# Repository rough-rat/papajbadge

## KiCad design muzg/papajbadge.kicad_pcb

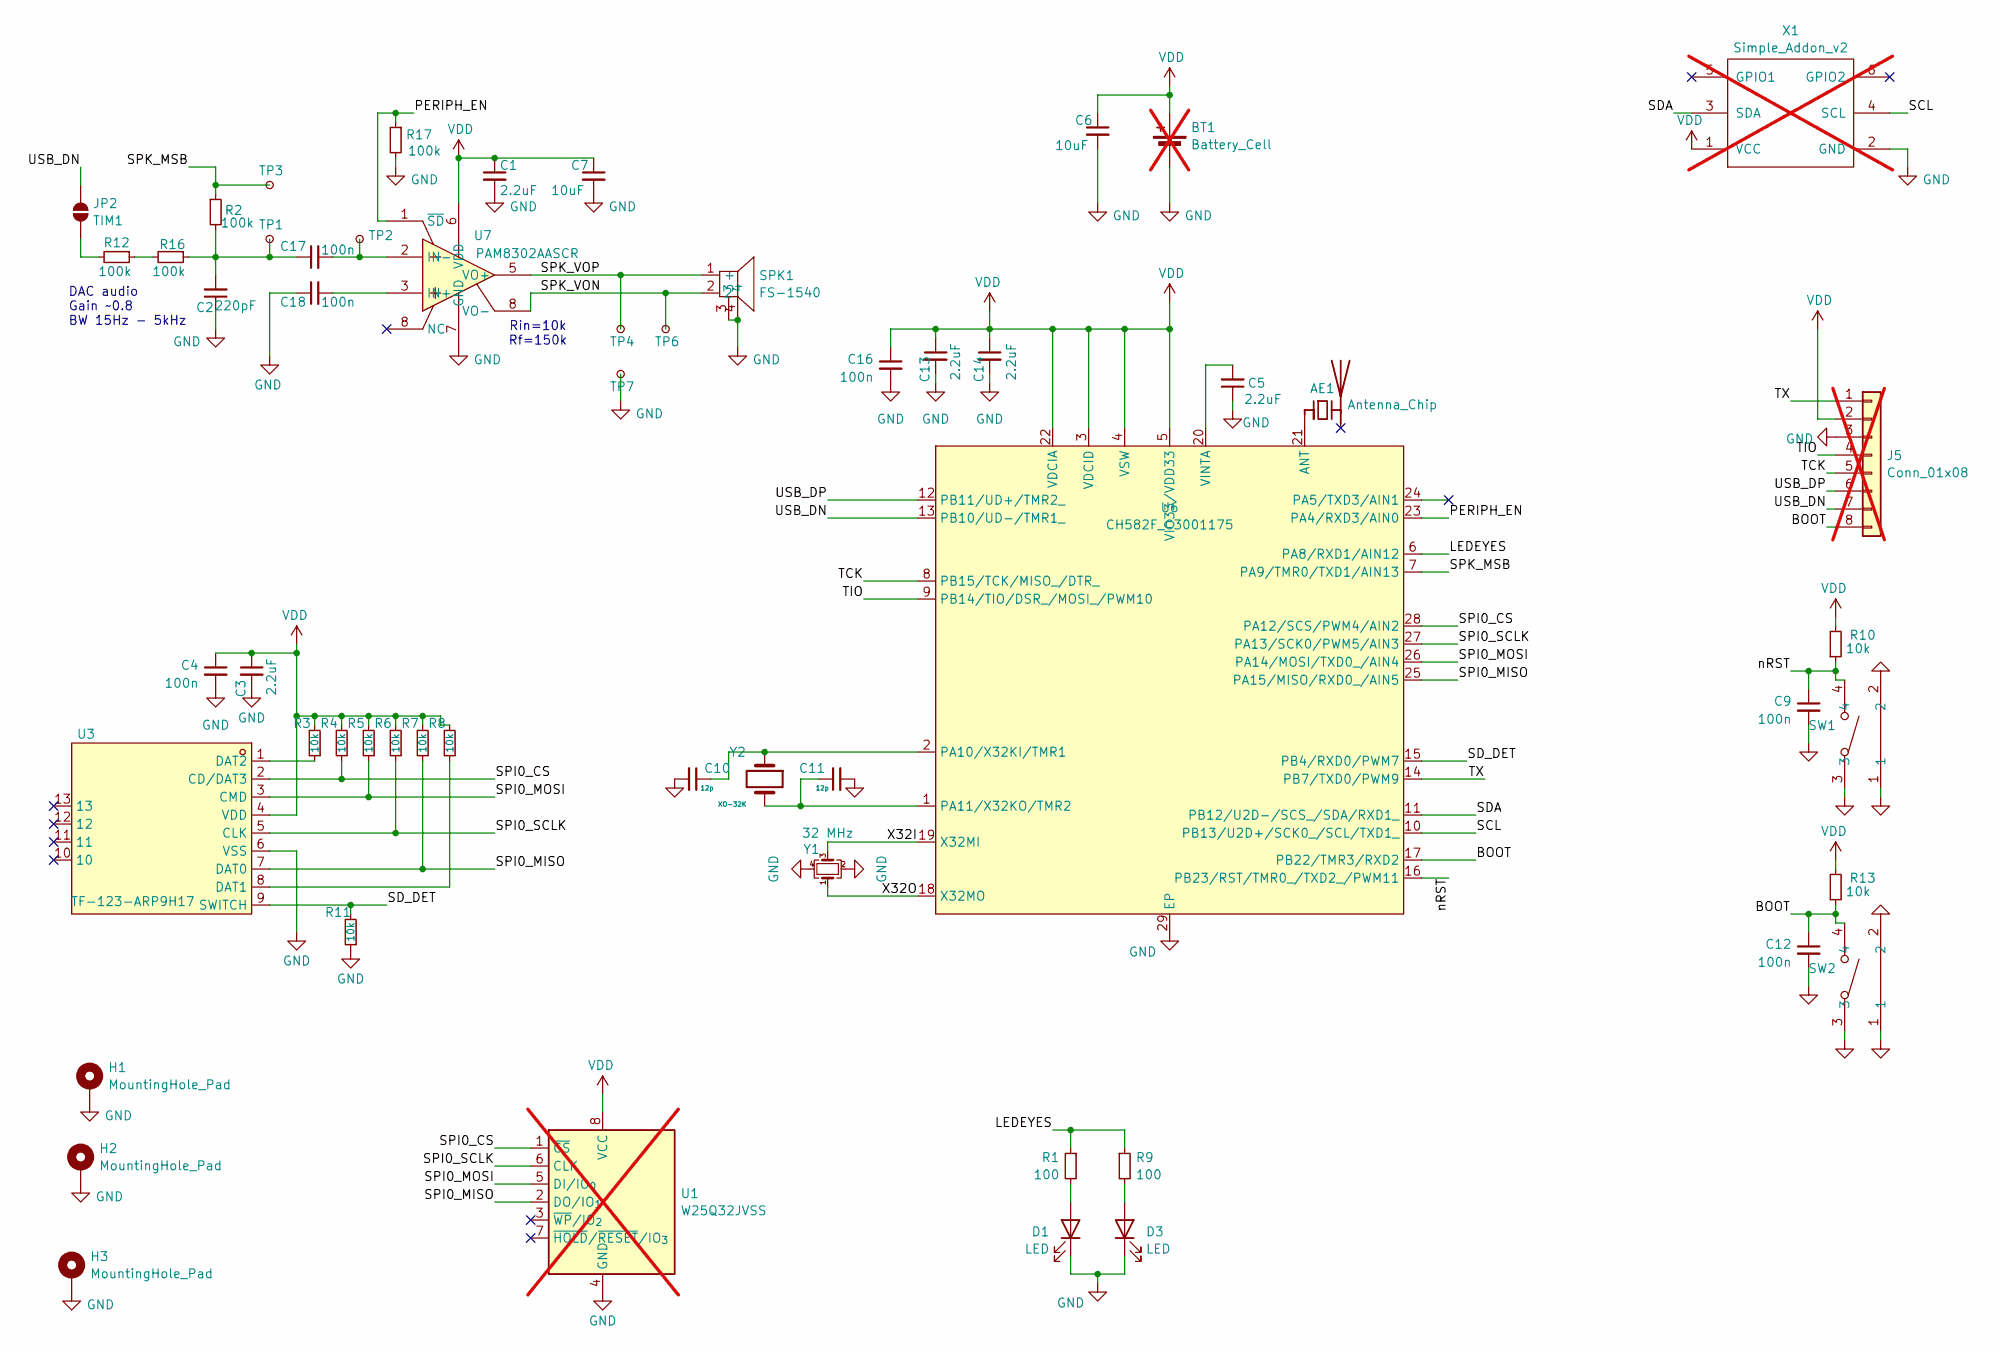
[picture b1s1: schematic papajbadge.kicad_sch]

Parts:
AE1: Antenna_Chip; Johanson_2450AT18x100; LCSC C127629
BT1: Battery_Cell; BatteryHolder_Multicomp_BC-2001_1x2032; not fitted
C1, C3, C5, C13, C14: 2.2uF; C_0402_1005Metric
C2: 220pF; C_0402_1005Metric
C4, C9, C12, C16, C17, C18: 100n; C_0402_1005Metric
C6, C7: 10uF; C_0603_1608Metric
C10, C11: 12p; C_0402_1005Metric
D1, D3: LED; LED_0603_1608Metric
H1, H2, H3: MountingHole_Pad; MountingHole_2.7mm_M2.5_DIN965_Pad
J5: Conn_01x08; PinSocket_1x08_P2.54mm_Vertical; not fitted
JP2: TIM1; SolderJumper-2_P1.3mm_Open_RoundedPad1.0x1.5mm
R1, R9: 100; R_0402_1005Metric
R2, R12, R16, R17: 100k; R_0402_1005Metric
R3, R4, R5, R6, R7, R8, R10, R11, R13: 10k; R_0402_1005Metric
SPK1: FS-1540; BUZ-SMD_5P-L15.0-W15.0-P13.7-BL; LCSC C482341
SW1, SW2: TS24CA; SW-SMD_TS24CA; LCSC C393942
TP1, TP2, TP3: RX; TestPoint_Pad_D0.6mm
TP4, TP6, TP7: RX; TestPoint_Pad_D1.0mm
U1: W25Q32JVSS; SOIC-8_5.3x5.3mm_P1.27mm; not fitted
U3: TF-123-ARP9H17; TF-SMD_TF-123-ARP9H15; LCSC C2982548
U6: CH582F_C3001175; QFN-28_L4.0-W4.0-P0.40-BL-EP2.8; LCSC C3001175
U7: PAM8302AASCR; MSOP-8_L3.0-W3.0-P0.65-LS5.0-BL; LCSC C113367
X1: Simple_Addon_v2; PinHeader_2x03_P2.54mm_Vertical; not fitted
Y1: 32 MHz; Crystal_SMD_2016-4Pin_2.0x1.6mm; LCSC C2682773
Y2: XO-32K; Crystal_SMD_2012-2Pin_2.0x1.2mm; LCSC C7500573

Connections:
/BOOT: C12.1, J5.8, R13.1, SW2.4, U6.17 (PB22/TMR3/RXD2)
/LEDEYES: R1.1, R9.1, U6.6 (PA8/RXD1/AIN12)
/PERIPH_EN: R17.1, U6.23 (PA4/RXD3/AIN0), U7.1 (~SD)
/SCL: U6.10 (PB13/U2D+/SCK0_/SCL/TXD1_), X1.4 (SCL)
/SDA: U6.11 (PB12/U2D-/SCS_/SDA/RXD1_), X1.3 (SDA)
/SD_DET: R11.2, U3.9 (SWITCH), U6.15 (PB4/RXD0/PWM7)
/SPI0_CS: R4.1, U1.1 (~CS), U3.2 (CD/DAT3), U6.28 (PA12/SCS/PWM4/AIN2)
/SPI0_MISO: R7.1, U1.2 (DO/IO_{1}), U3.7 (DAT0), U6.25 (PA15/MISO/RXD0_/AIN5)
/SPI0_MOSI: R5.1, U1.5 (DI/IO_{0}), U3.3 (CMD), U6.26 (PA14/MOSI/TXD0_/AIN4)
/SPI0_SCLK: R6.1, U1.6 (CLK), U3.5 (CLK), U6.27 (PA13/SCK0/PWM5/AIN3)
/SPK_MSB: R2.1, TP3.1, U6.7 (PA9/TMR0/TXD1/AIN13)
/SPK_VON: SPK1.2, TP6.1, U7.8 (VO-)
/SPK_VOP: SPK1.1 (+), TP4.1, U7.5 (VO+)
/TCK: J5.5, U6.8 (PB15/TCK/MISO_/DTR_)
/TIO: J5.4, U6.9 (PB14/TIO/DSR_/MOSI_/PWM10)
/TX: J5.1, U6.14 (PB7/TXD0/PWM9)
/USB_DN: J5.7, JP2.2 (B), U6.13 (PB10/UD-/TMR1_)
/USB_DP: J5.6, U6.12 (PB11/UD+/TMR2_)
/X32I: U6.19 (X32MI), Y1.3
/X32O: U6.18 (X32MO), Y1.1
/nRST: C9.1, R10.1, SW1.4, U6.16 (PB23/RST/TMR0_/TXD2_/PWM11)
GND: BT1.2 (-), C1.2, C2.1, C3.2, C4.2, C5.1, C6.2, C7.2, C9.2, C10.2, C11.2, C12.2, C13.2, C14.2, C16.2, C18.1, D1.1 (K), D3.1 (K), H1.1, H2.1, H3.1, J5.3, R11.1, R17.2, SPK1.3, SPK1.4, SW1.1, SW1.2, SW1.3, SW2.1, SW2.2, SW2.3, TP7.1, U1.4 (GND), U3.6 (VSS), U6.29 (EP), U7.7 (GND), X1.2 (GND), Y1.2, Y1.4
unnamed: AE1.1 (FEED), U6.21 (ANT)
unnamed: C2.2, C17.1, R2.2, R16.1, TP1.1
unnamed: D1.2 (A), R1.2
unnamed: D3.2 (A), R9.2
unnamed: JP2.1 (A), R12.2
unnamed: R12.1, R16.2
unnamed: R8.1, U3.8 (DAT1)
unnamed: R3.1, U3.1 (DAT2)
unnamed: C10.1, U6.2 (PA10/X32KI/TMR1), Y2.1
unnamed: C11.1, U6.1 (PA11/X32KO/TMR2), Y2.2
unnamed: C5.2, U6.20 (VINTA)
unnamed: C18.2, U7.3 (IN+)
unnamed: C17.2, TP2.1, U7.2 (IN-)
VDD: BT1.1 (+), C1.1, C3.1, C4.1, C6.1, C7.1, C13.1, C14.1, C16.1, J5.2, R3.2, R4.2, R5.2, R6.2, R7.2, R8.2, R10.2, R13.2, U1.8 (VCC), U3.4 (VDD), U6.3 (VDCID), U6.4 (VSW), U6.5 (VIO33/VDD33), U6.22 (VDCIA), U7.6 (VDD), X1.1 (VCC)

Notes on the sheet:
Rin=10k Rf=150k
DAC audio Gain ~0.8 BW 15Hz - 5kHz

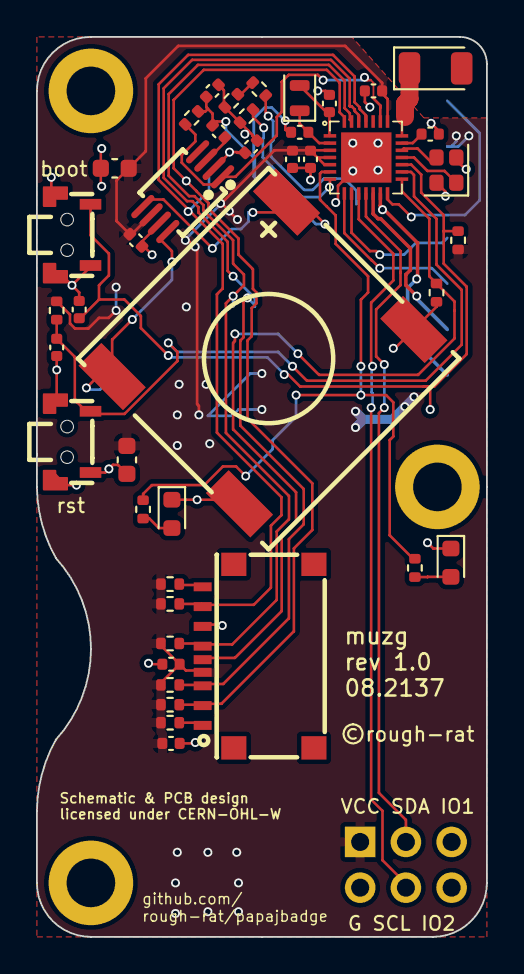
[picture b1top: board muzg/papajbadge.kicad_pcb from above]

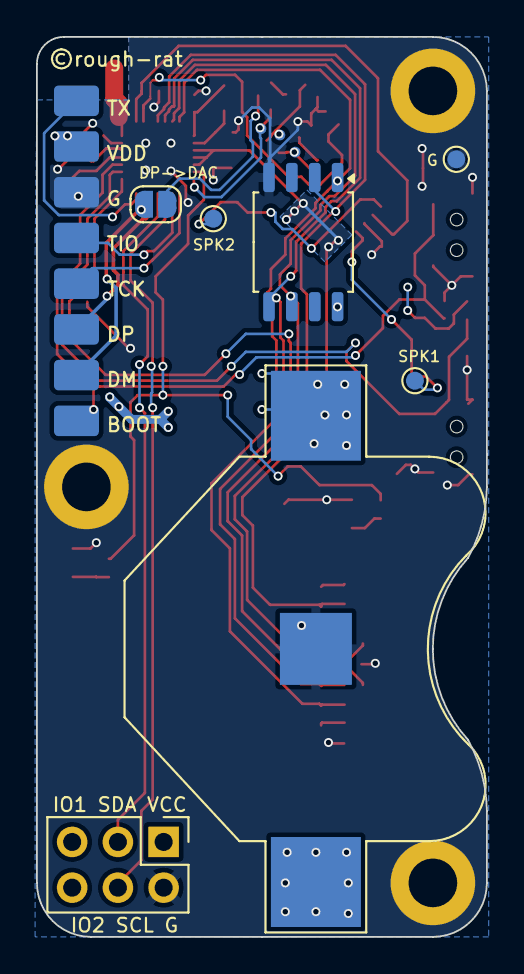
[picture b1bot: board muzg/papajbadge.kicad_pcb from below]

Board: 2 copper layers, 25.0 x 50.0 mm, 56 parts (12 on the bottom side), 36 nets.

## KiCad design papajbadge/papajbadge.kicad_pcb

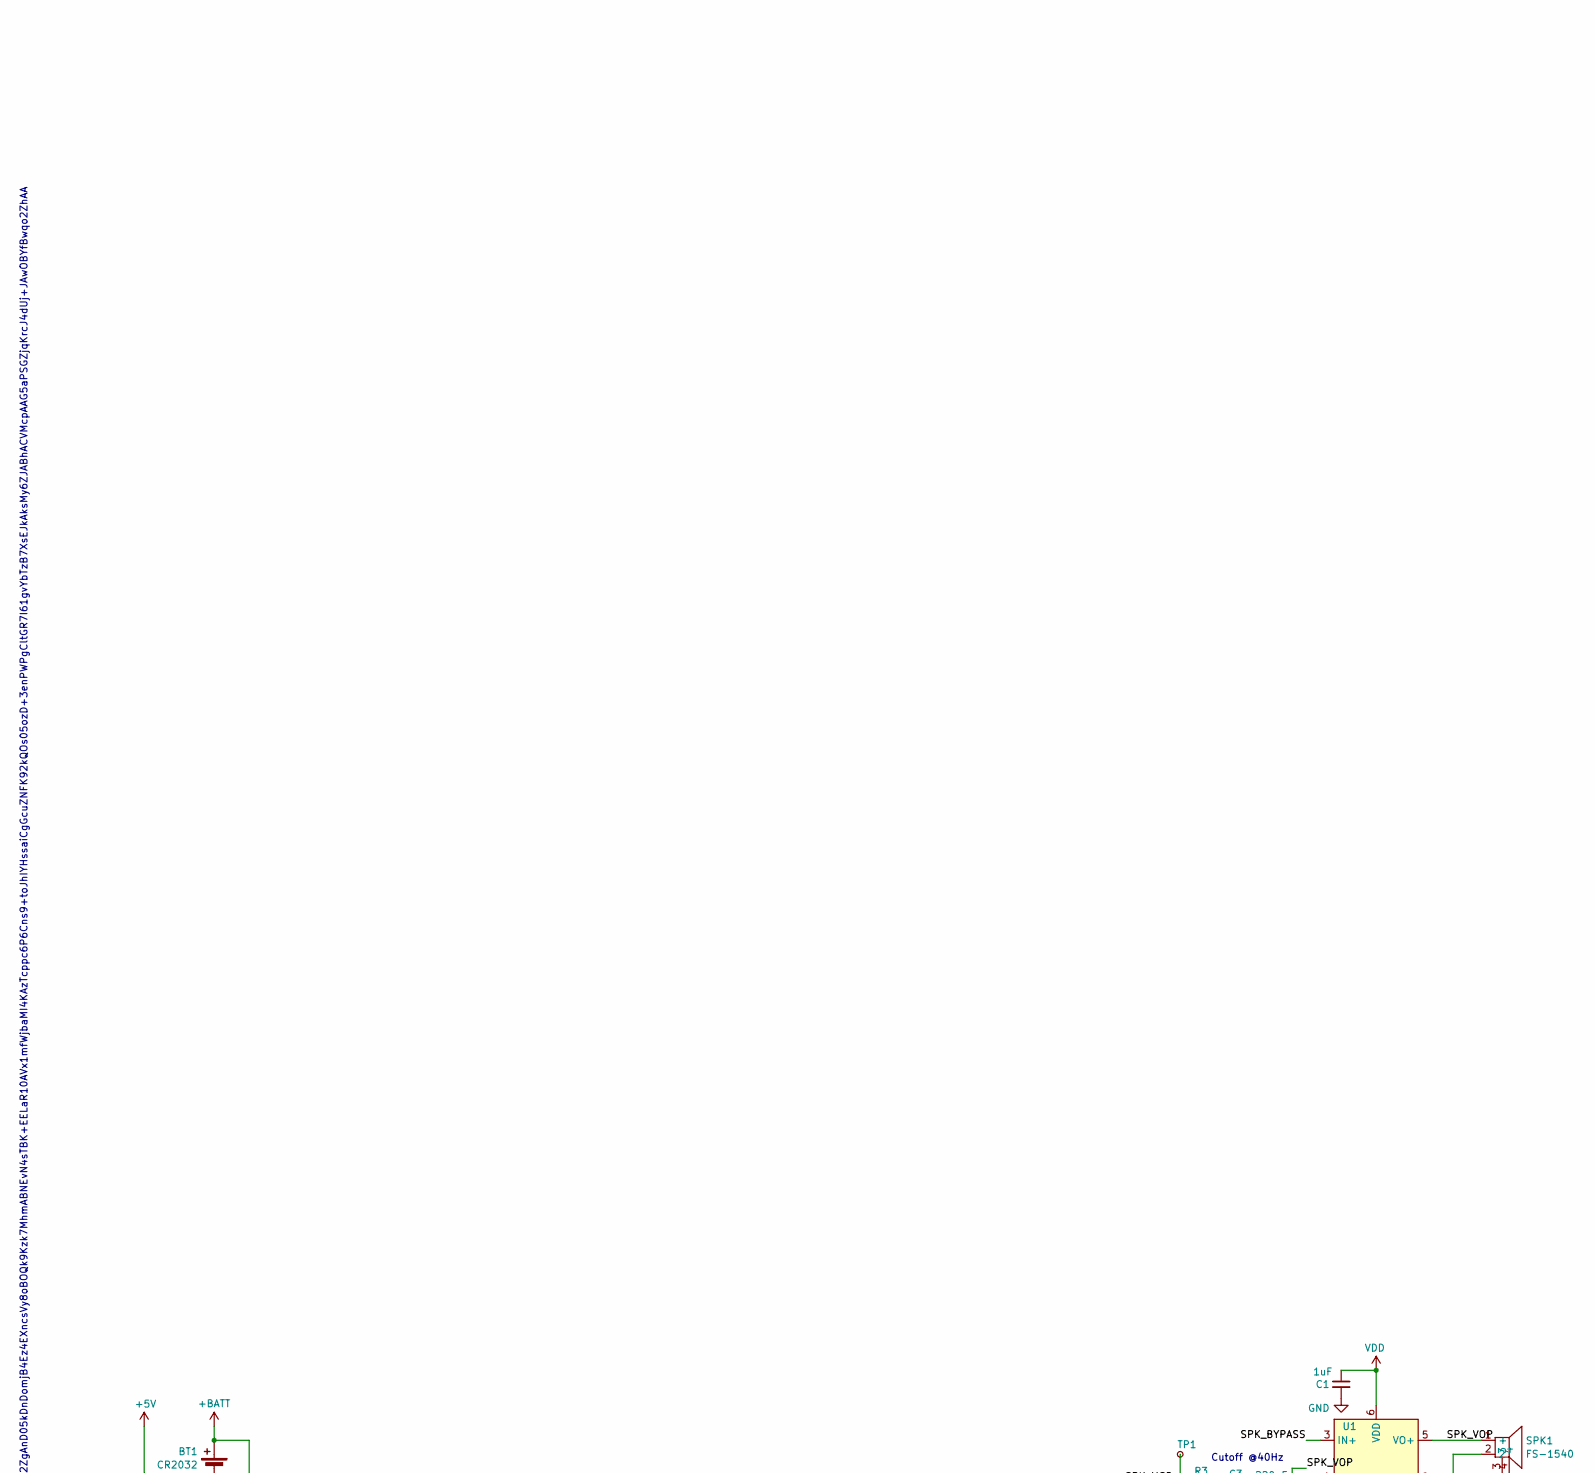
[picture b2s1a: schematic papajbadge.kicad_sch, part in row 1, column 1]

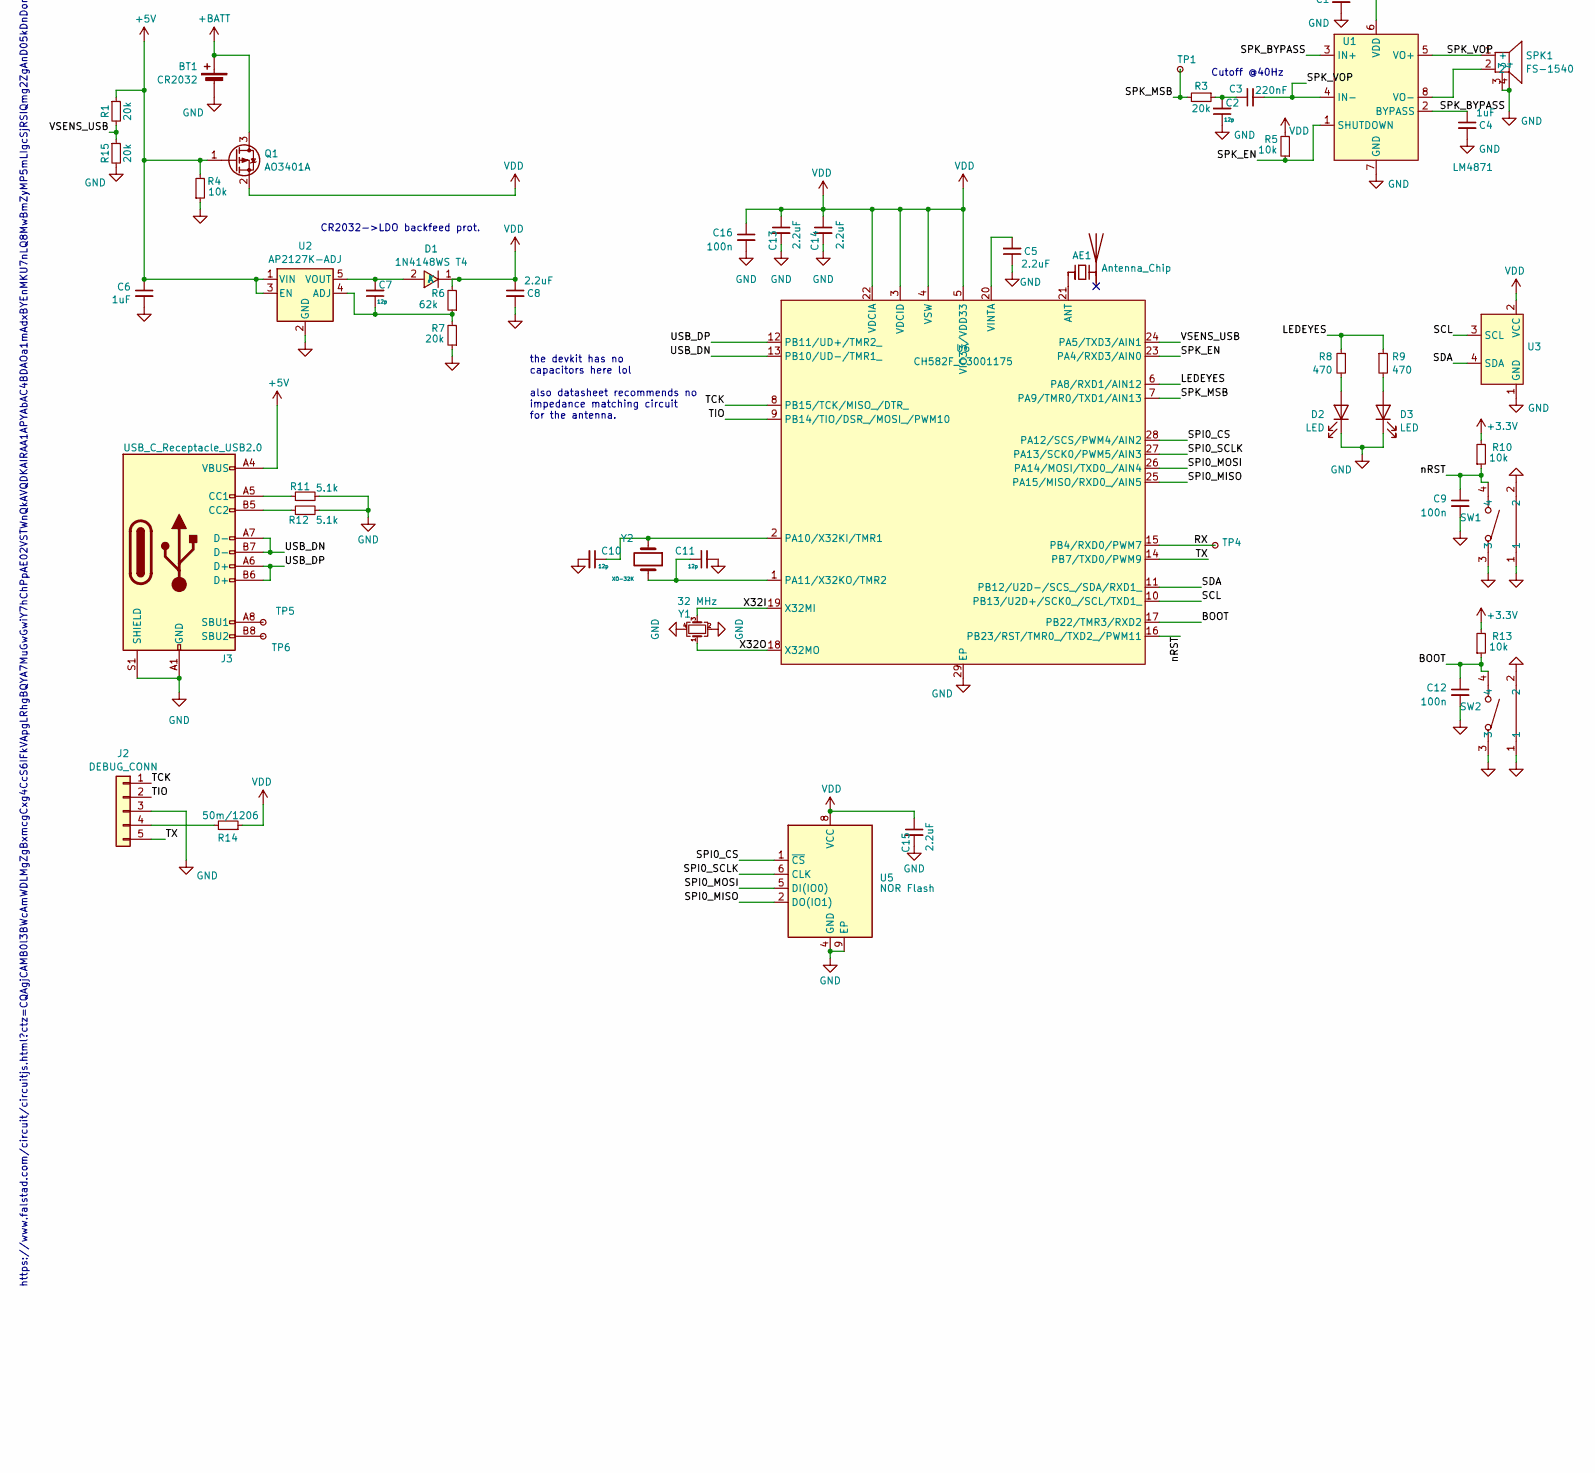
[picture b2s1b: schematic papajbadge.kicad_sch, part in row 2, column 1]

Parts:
AE1: Antenna_Chip; Johanson_2450AT18x100; LCSC C127629
BT1: CR2032; BatteryHolder_Multicomp_BC-2001_1x2032
C1, C4: 1uF; C_0402_1005Metric
C2, C7, C10, C11: 12p; C_0402_1005Metric; LCSC C1547
C3: 220nF; C_0402_1005Metric
C5, C8, C13, C14, C15: 2.2uF; C_0402_1005Metric
C6: 1uF; C_0402_1005Metric; LCSC C52923
C9, C12, C16: 100n; C_0402_1005Metric; LCSC C1525
D1: 1N4148WS T4; SOD-323_L1.8-W1.3-LS2.5-RD; LCSC Part C2128
D2, D3: LED; eyeled
J2: DEBUG_CONN; PinHeader_1x05_P2.54mm_Vertical
J3: USB_C_Receptacle_USB2.0; USB_C_Receptacle_HRO_TYPE-C-31-M-12; LCSC C165948
Q1: AO3401A; SOT-23
R1, R3, R7, R15: 20k; R_0402_1005Metric; LCSC C25741
R4, R5: 10k; R_0402_1005Metric; LCSC C25741
R6: 62k; R_0805_2012Metric; LCSC C17783
R8, R9: 470; LED_0805_2012Metric_Pad1.15x1.40mm_HandSolder
R10, R13: 10k; R_0402_1005Metric
R11, R12: 5.1k; R_0402_1005Metric
R14: 50m/1206; R_1206_3216Metric
SPK1: FS-1540; BUZ-SMD_5P-L15.0-W15.0-P13.7-BL; LCSC Part C482341
SW1, SW2: TS24CA; SW-SMD_TS24CA; LCSC C393942
TP1, TP4, TP5, TP6: RX; TestPoint_Pad_D0.6mm
U1: LM4871; SOIC-8_L4.9-W3.9-P1.27-LS6.0-BL; LCSC Part C7494970
U2: AP2127K-ADJ; SOT-23-5; LCSC C96343
U3: PinHeader_1x04_P2.54mm_Vertical
U5: NOR Flash; USON-8_2x3; LCSC C2843335
U6: CH582F_C3001175; QFN-28_L4.0-W4.0-P0.40-BL-EP2.8; LCSC Part C3001175
Y1: 32 MHz; Crystal_SMD_2016-4Pin_2.0x1.6mm
Y2: XO-32K; Crystal_SMD_2012-2Pin_2.0x1.2mm; LCSC C7500573

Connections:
+3.3V: R10.2, R13.2
+5V: C6.1, J3.A4 (VBUS), J3.A9 (VBUS), J3.B4 (VBUS), J3.B9 (VBUS), Q1.1 (G), R1.1, R4.2, U2.1 (VIN), U2.3 (EN)
+BATT: BT1.1 (+), Q1.3 (D)
/BOOT: C12.1, R13.1, SW2.4, U6.17 (PB22/TMR3/RXD2)
/LEDEYES: R8.1, R9.1, U6.6 (PA8/RXD1/AIN12)
/RX: TP4.1, U6.15 (PB4/RXD0/PWM7)
/SCL: U3.3 (SCL), U6.10 (PB13/U2D+/SCK0_/SCL/TXD1_)
/SDA: U3.4 (SDA), U6.11 (PB12/U2D-/SCS_/SDA/RXD1_)
/SPI0_CS: U5.1 (~CS), U6.28 (PA12/SCS/PWM4/AIN2)
/SPI0_MISO: U5.2 (DO(IO1)), U6.25 (PA15/MISO/RXD0_/AIN5)
/SPI0_MOSI: U5.5 (DI(IO0)), U6.26 (PA14/MOSI/TXD0_/AIN4)
/SPI0_SCLK: U5.6 (CLK), U6.27 (PA13/SCK0/PWM5/AIN3)
/SPK_BYPASS: C4.1, U1.2 (BYPASS), U1.3 (IN+)
/SPK_EN: R5.1, U1.1 (SHUTDOWN), U6.23 (PA4/RXD3/AIN0)
/SPK_MSB: R3.2, TP1.1, U6.7 (PA9/TMR0/TXD1/AIN13)
/SPK_VOP: C3.2, SPK1.1 (+), U1.4 (IN-), U1.5 (VO+)
/TCK: J2.1, U6.8 (PB15/TCK/MISO_/DTR_)
/TIO: J2.2, U6.9 (PB14/TIO/DSR_/MOSI_/PWM10)
/TX: J2.5, U6.14 (PB7/TXD0/PWM9)
/USB_DN: J3.A7 (D-), J3.B7 (D-), U6.13 (PB10/UD-/TMR1_)
/USB_DP: J3.A6 (D+), J3.B6 (D+), U6.12 (PB11/UD+/TMR2_)
/VSENS_USB: R1.2, R15.1, U6.24 (PA5/TXD3/AIN1)
/X32I: U6.19 (X32MI), Y1.3
/X32O: U6.18 (X32MO), Y1.1
/nRST: C9.1, R10.1, SW1.4, U6.16 (PB23/RST/TMR0_/TXD2_/PWM11)
GND: BT1.2 (-), C1.2, C2.1, C4.2, C5.1, C6.2, C8.2, C9.2, C10.2, C11.2, C12.2, C13.2, C14.2, C15.2, C16.2, D2.1 (K), D3.1 (K), J2.3, J3.A1 (GND), J3.A12 (GND), J3.B1 (GND), J3.B12 (GND), J3.S1 (SHIELD), R4.1, R7.1, R11.2, R12.2, R15.2, SPK1.3, SPK1.4, SW1.1, SW1.2, SW1.3, SW2.1, SW2.2, SW2.3, U1.7 (GND), U2.2 (GND), U3.1 (GND), U5.4 (GND), U5.9 (EP), U6.29 (EP), Y1.2, Y1.4
unnamed: AE1.1 (FEED), U6.21 (ANT)
unnamed: C2.2, C3.1, R3.1
unnamed: C7.2, D1.2 (A), U2.5 (VOUT)
unnamed: D2.2 (A), R8.2
unnamed: D3.2 (A), R9.2
unnamed: J2.4, R14.2
unnamed: J3.A5 (CC1), R11.1
unnamed: J3.B5 (CC2), R12.1
unnamed: J3.A8 (SBU1), TP5.1
unnamed: J3.B8 (SBU2), TP6.1
unnamed: SPK1.2, U1.8 (VO-)
unnamed: C7.1, R6.1, R7.2, U2.4 (ADJ)
unnamed: C10.1, U6.2 (PA10/X32KI/TMR1), Y2.1
unnamed: C11.1, U6.1 (PA11/X32KO/TMR2), Y2.2
unnamed: C5.2, U6.20 (VINTA)
VDD: C1.1, C8.1, C13.1, C14.1, C15.1, C16.1, D1.1 (K), Q1.2 (S), R5.2, R6.2, R14.1, U1.6 (VDD), U3.2 (VCC), U5.8 (VCC), U6.3 (VDCID), U6.4 (VSW), U6.5 (VIO33/VDD33), U6.22 (VDCIA)

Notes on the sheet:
CR2032->LDO backfeed prot.
Cutoff @40Hz
the devkit has no capacitors here lol also datasheet recommends no impedance matching circuit for the antenna.
https://www.falstad.com/circuit/circuitjs.html?ctz=CQAgjCAMB0l3BWcAmWDLMgZgBxmcgCxg4CcS6IFkVApgLRhgBQYA7MuGwGwiY7hChPpAE02VSTWnQkAVQDKAIRAA1APYAbAC4BDAOa1mAdxBYEnMKU7nLQ8MwBmZyMP5mLIgcSjRSIQmg2ZgAnD05kDnDomjB4Ez4EXncsVy8oBOQk9Kzk7MhmABNEvN4sTBK+EELaR10AVx1mfWjbaMI4KAzTcppc6P6Cns9+toJhIYHssaiCgGcuZN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

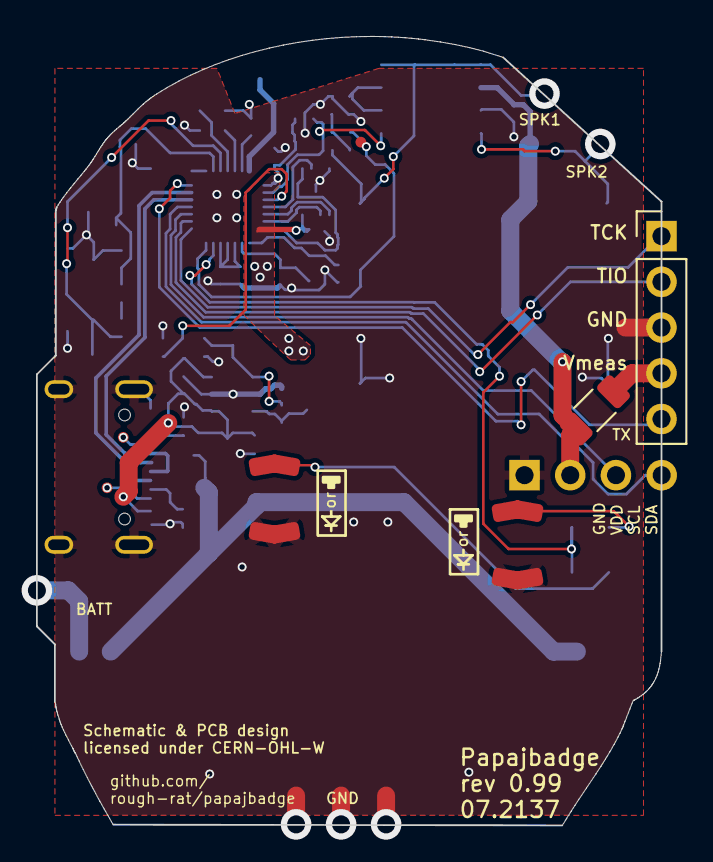
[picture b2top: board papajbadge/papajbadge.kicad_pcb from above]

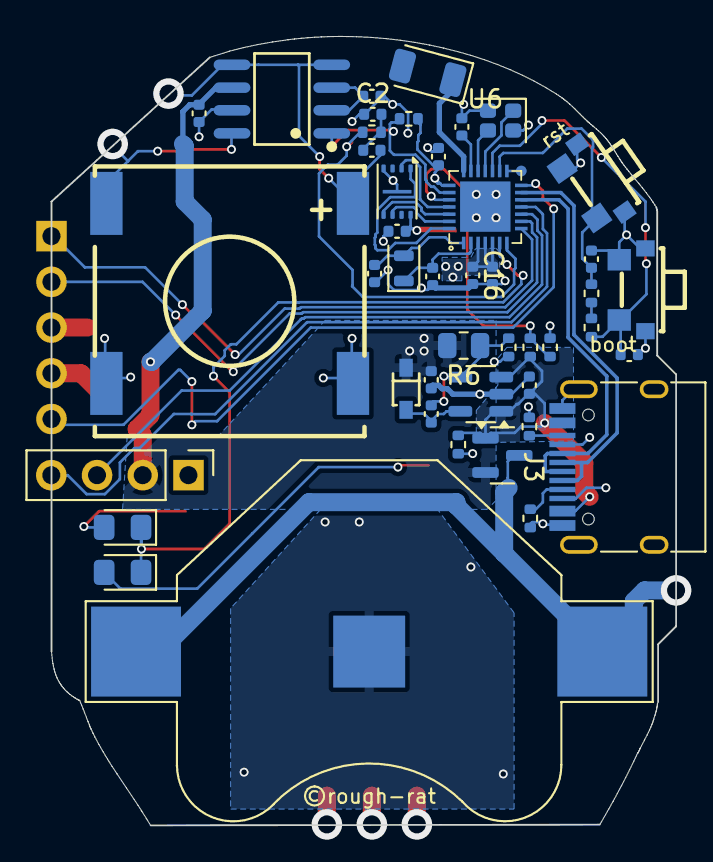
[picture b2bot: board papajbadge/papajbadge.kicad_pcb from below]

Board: 2 copper layers, 34.7 x 43.8 mm, 52 parts (45 on the bottom side), 42 nets.

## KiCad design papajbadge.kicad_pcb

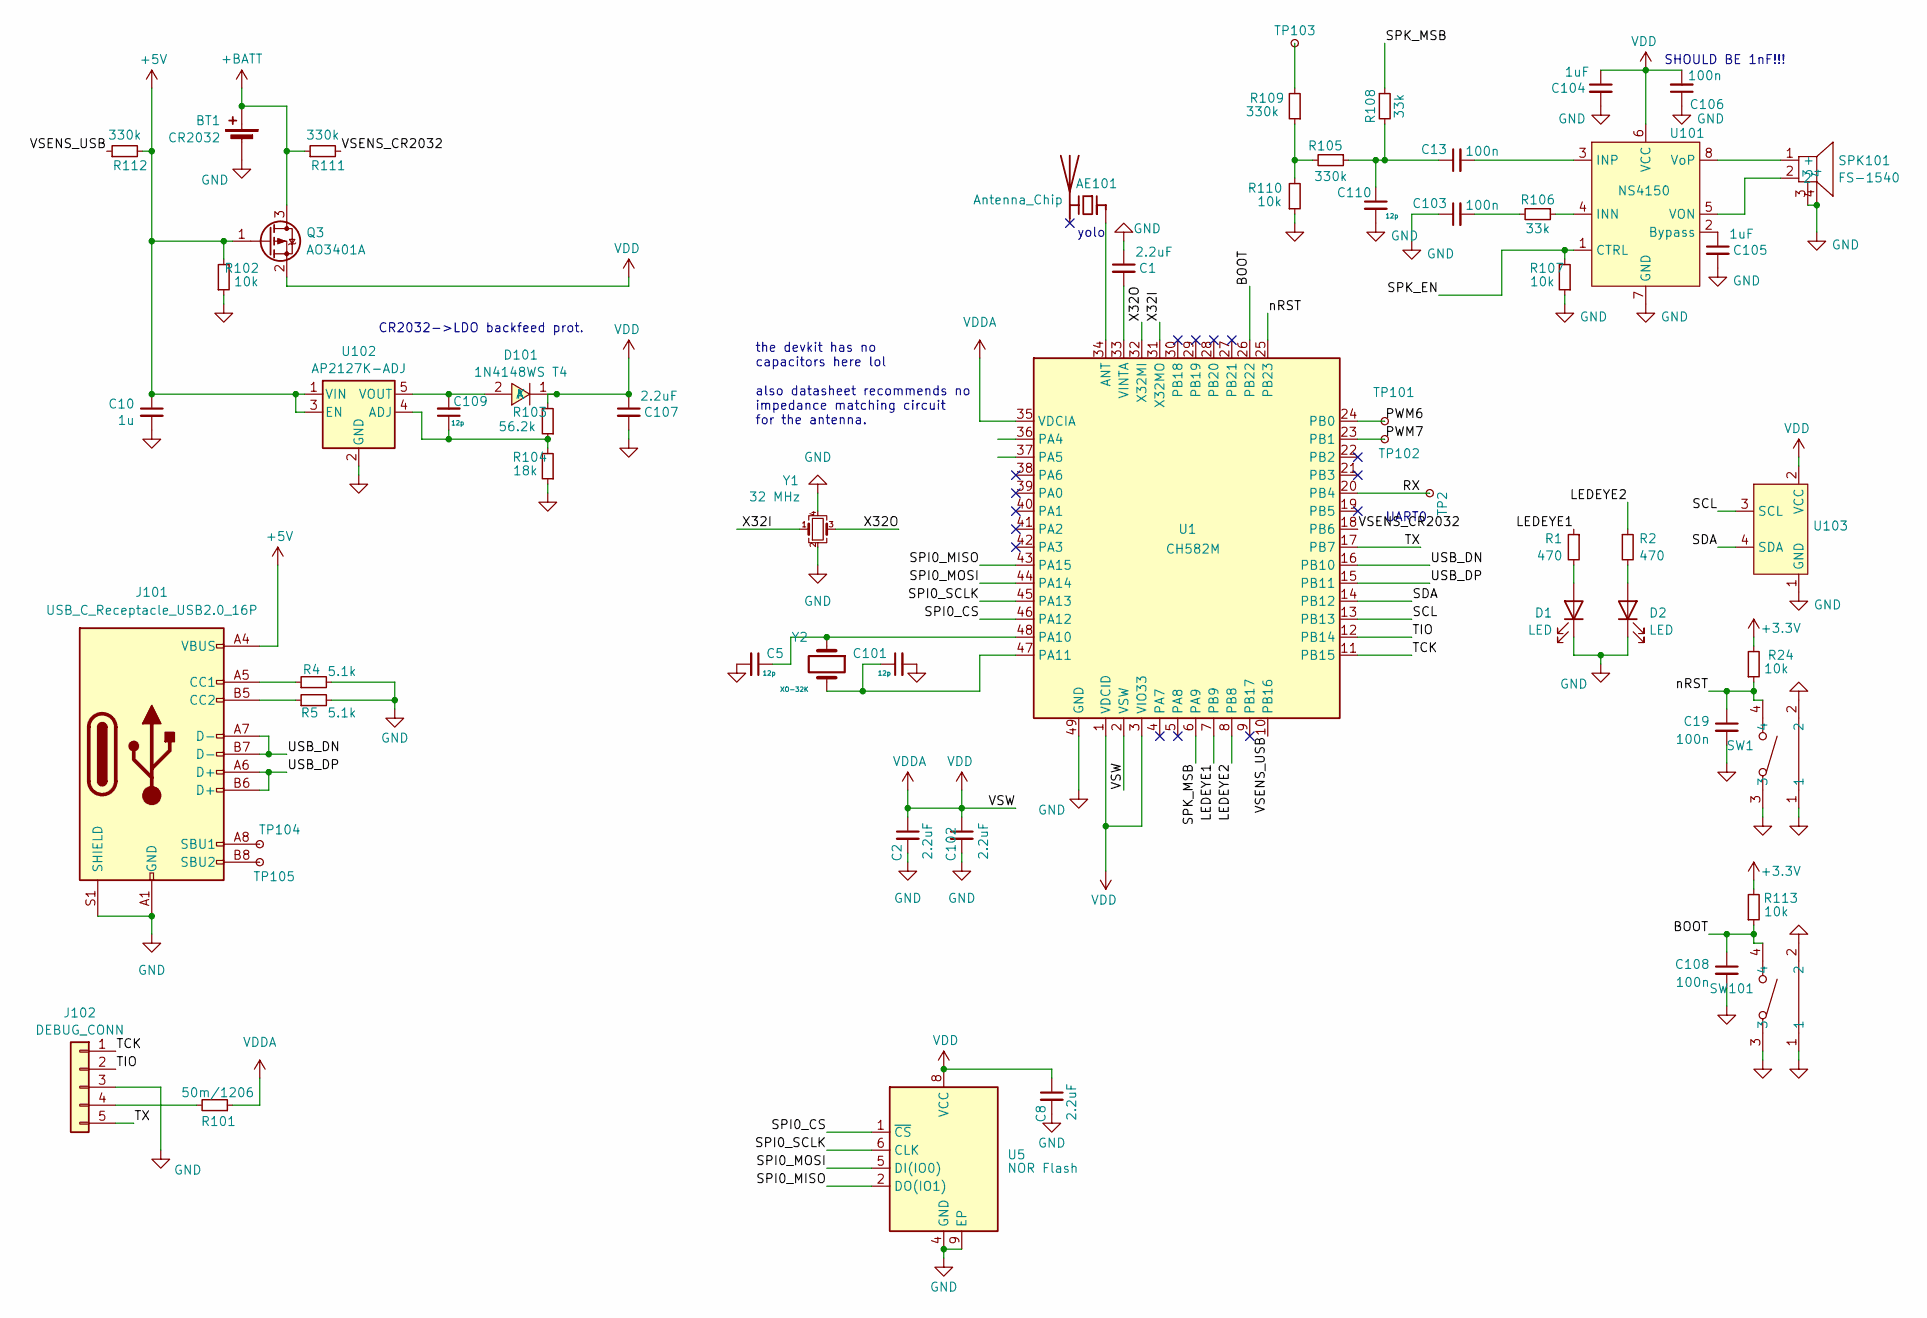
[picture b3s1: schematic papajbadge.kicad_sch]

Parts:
AE101: Antenna_Chip; Johanson_2450AT18x100; LCSC C127629
BT1: CR2032; BatteryHolder_Multicomp_BC-2001_1x2032
C1, C2, C8, C102, C107: 2.2uF; C_0402_1005Metric
C5, C101, C109, C110: 12p; C_0402_1005Metric; LCSC C1547
C10: 1u; C_0402_1005Metric; LCSC C52923
C13, C103, C106: 100n; C_0402_1005Metric
C19, C108: 100n; C_0402_1005Metric; LCSC C1525
C104, C105: 1uF; C_0402_1005Metric
D1, D2: LED; eyeled
D101: 1N4148WS T4; SOD-323_L1.8-W1.3-LS2.5-RD; LCSC Part C2128
J101: USB_C_Receptacle_USB2.0_16P; USB_C_Receptacle_GCT_USB4110
J102: DEBUG_CONN; PinHeader_1x05_P2.54mm_Vertical
Q3: AO3401A; SOT-23
R1, R2: 470; LED_0805_2012Metric_Pad1.15x1.40mm_HandSolder
R4, R5: 5.1k; R_0402_1005Metric
R24, R113: 10k; R_0402_1005Metric
R101: 50m/1206; R_1206_3216Metric
R102, R107, R110: 10k; R_0402_1005Metric; LCSC C25741
R103: 56.2k; R_0402_1005Metric; LCSC C25741
R104: 18k; R_0402_1005Metric; LCSC C25741
R105, R109, R111, R112: 330k; R_0402_1005Metric; LCSC C25741
R106, R108: 33k; R_0402_1005Metric; LCSC C25741
SPK101: FS-1540; BUZ-SMD_5P-L15.0-W15.0-P13.7-BL; LCSC Part C482341
SW1, SW101: TS24CA; SW-SMD_TS24CA; LCSC C393942
TP2, TP101, TP102, TP103, TP104, TP105: RX; TestPoint_Pad_D0.6mm
U1: CH582M; CH582-QFN-48-1EP_5x5mm_P0.35mm_EP3.7x3.7mm
U5: NOR Flash; USON-8_2x3; LCSC C2843335
U101: NS4150; MSOP-8_L3.0-W3.0-P0.65-LS5.0-BL; LCSC Part C189961
U102: AP2127K-ADJ; SOT-23-5; LCSC C96343
U103: PinHeader_1x04_P2.54mm_Vertical
Y1: 32 MHz; Crystal_SMD_2016-4Pin_2.0x1.6mm
Y2: XO-32K; Crystal_SMD_2012-2Pin_2.0x1.2mm; LCSC C7500573

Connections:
+3.3V: R24.2, R113.2
+5V: C10.1, J101.A4 (VBUS), J101.A9 (VBUS), J101.B4 (VBUS), J101.B9 (VBUS), Q3.1 (G), R102.2, R112.2, U102.1 (VIN), U102.3 (EN)
+BATT: BT1.1 (+), Q3.3 (D), R111.1
/BOOT: C108.1, R113.1, SW101.4, U1.26 (PB22)
/LEDEYE1: R1.1, U1.7 (PB9)
/LEDEYE2: R2.1, U1.8 (PB8)
/PWM6: TP101.1, U1.24 (PB0)
/PWM7: TP102.1, U1.23 (PB1)
/RX: TP2.1, U1.20 (PB4)
/SCL: U1.13 (PB13), U103.3 (SCL)
/SDA: U1.14 (PB12), U103.4 (SDA)
/SPI0_CS: U1.46 (PA12), U5.1 (~CS)
/SPI0_MISO: U1.43 (PA15), U5.2 (DO(IO1))
/SPI0_MOSI: U1.44 (PA14), U5.5 (DI(IO0))
/SPI0_SCLK: U1.45 (PA13), U5.6 (CLK)
/SPK_EN: R107.2, U101.1 (CTRL)
/SPK_MSB: R108.1, U1.6 (PA9)
/TCK: J102.1, U1.11 (PB15)
/TIO: J102.2, U1.12 (PB14)
/TX: J102.5, U1.17 (PB7)
/USB_DN: J101.A7 (D-), J101.B7 (D-), U1.16 (PB10)
/USB_DP: J101.A6 (D+), J101.B6 (D+), U1.15 (PB11)
/VSENS_CR2032: R111.2, U1.18 (PB6)
/VSENS_USB: R112.1, U1.10 (PB16)
/X32I: U1.31 (X32MO), Y1.1
/X32O: U1.32 (X32MI), Y1.3
/nRST: C19.1, R24.1, SW1.4, U1.25 (PB23)
GND: BT1.2 (-), C1.1, C2.2, C5.2, C8.2, C10.2, C19.2, C101.2, C102.2, C103.1, C104.2, C105.2, C106.1, C107.2, C108.2, C110.2, D1.1 (K), D2.1 (K), J101.A1 (GND), J101.A12 (GND), J101.B1 (GND), J101.B12 (GND), J101.S1 (SHIELD), J102.3, R4.2, R5.2, R102.1, R104.1, R107.1, R110.1, SPK101.3, SPK101.4, SW1.1, SW1.2, SW1.3, SW101.1, SW101.2, SW101.3, U1.49 (GND), U5.4 (GND), U5.9 (EP), U101.7 (GND), U102.2 (GND), U103.1 (GND), Y1.2, Y1.4
unnamed: AE101.1 (FEED), U1.34 (ANT)
unnamed: C13.1, C110.1, R105.1, R108.2
unnamed: C103.2, R106.2
unnamed: D1.2 (A), R1.2
unnamed: D2.2 (A), R2.2
unnamed: C109.2, D101.2 (A), U102.5 (VOUT)
unnamed: J101.A5 (CC1), R4.1
unnamed: J101.B5 (CC2), R5.1
unnamed: J101.A8 (SBU1), TP104.1
unnamed: J101.B8 (SBU2), TP105.1
unnamed: J102.4, R101.2
unnamed: R105.2, R109.1, R110.2
unnamed: R109.2, TP103.1
unnamed: SPK101.1 (+), U101.8 (VoP)
unnamed: C5.1, U1.48 (PA10), Y2.1
unnamed: C101.1, U1.47 (PA11), Y2.2
unnamed: C1.2, U1.33 (VINTA)
unnamed: C105.1, U101.2 (Bypass)
unnamed: R106.1, U101.4 (INN)
unnamed: C13.2, U101.3 (INP)
unnamed: SPK101.2, U101.5 (VON)
unnamed: C109.1, R103.1, R104.2, U102.4 (ADJ)
VDD: C2.1, C8.1, C102.1, C104.1, C106.2, C107.1, D101.1 (K), Q3.2 (S), R101.1, R103.2, U1.1 (VDCID), U1.2 (VSW), U1.3 (VIO33), U1.35 (VDCIA), U5.8 (VCC), U101.6 (VCC), U103.2 (VCC)

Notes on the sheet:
CR2032->LDO backfeed prot.
yolo
UART0
SHOULD BE 1nF!!!
the devkit has no capacitors here lol also datasheet recommends no impedance matching circuit for the antenna.

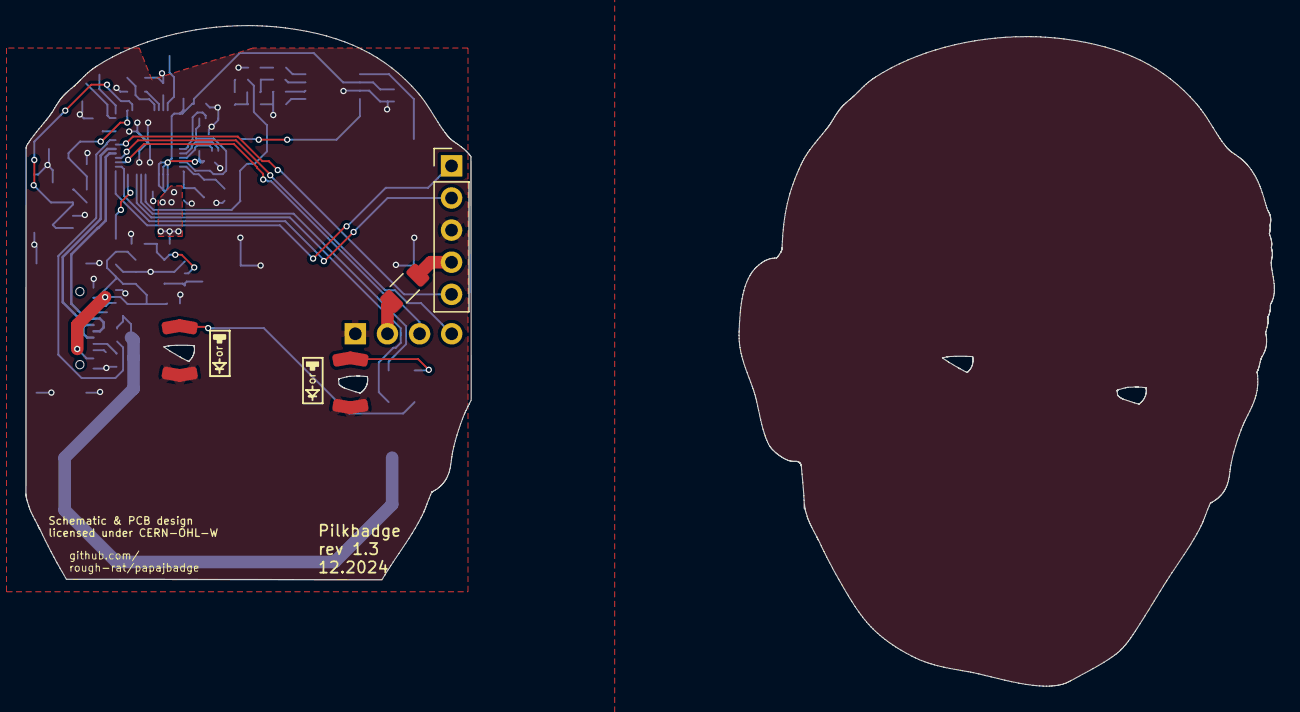
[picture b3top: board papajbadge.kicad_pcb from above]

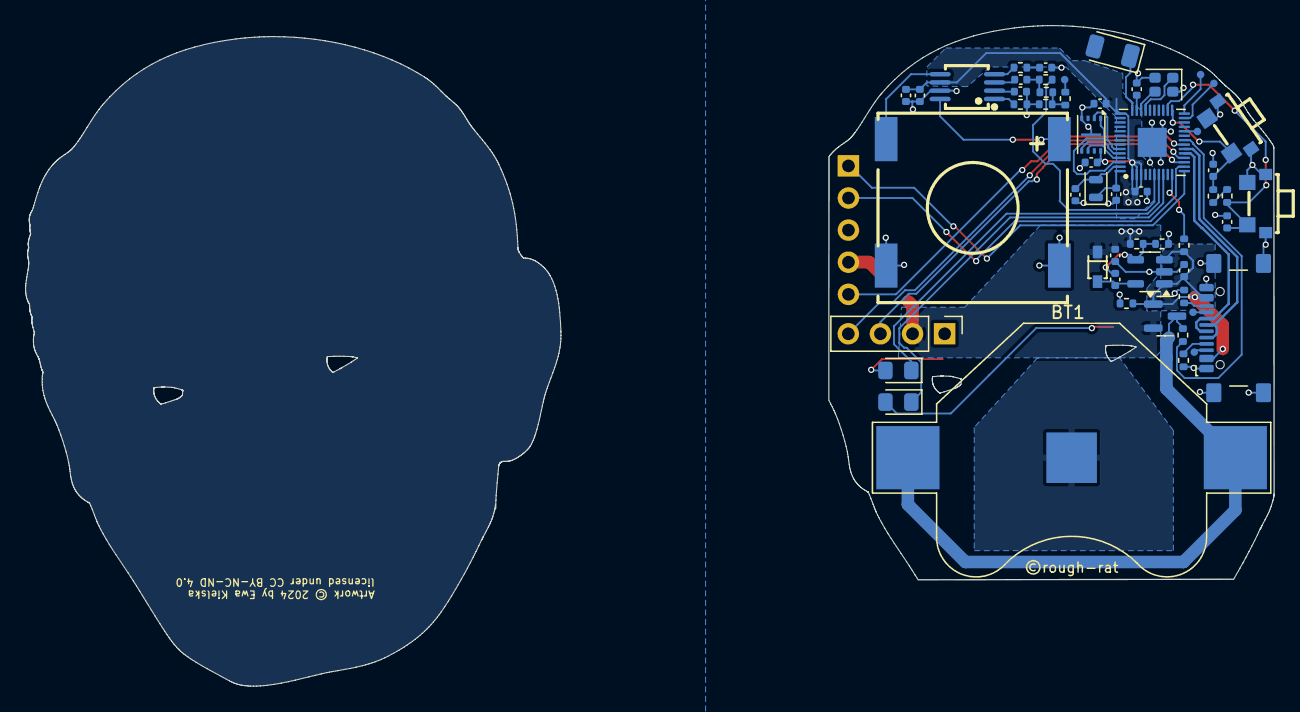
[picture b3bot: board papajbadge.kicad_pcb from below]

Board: 2 copper layers, 35.2 x 43.8 mm, 58 parts (54 on the bottom side), 51 nets.

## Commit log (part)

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2025-07-06 add blasphemy
2025-07-06 mostly finish sch and placement
2025-07-07 finish pcb before review
2025-07-08 before order
2025-07-09 swap ble mcu, commit before order
2025-08-09 add WIP files
2025-09-09 cebula releases

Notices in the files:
muzg/papajbadge.kicad_pcb:
©rough-rat
licensed under CERN-OHL-W
papajbadge.kicad_pcb:
Artwork © 2024 by Ewa Kielska
licensed under CC BY-NC-ND 4.0
